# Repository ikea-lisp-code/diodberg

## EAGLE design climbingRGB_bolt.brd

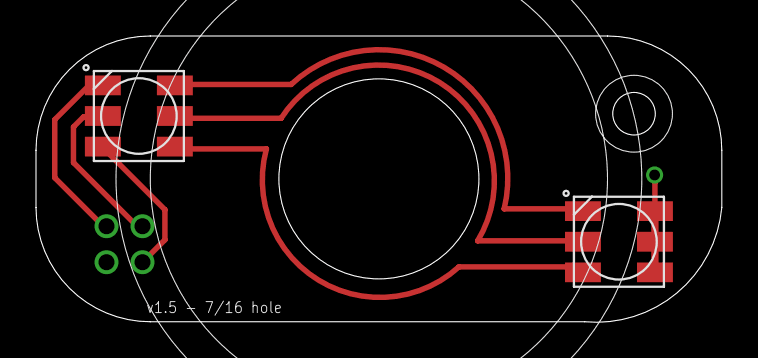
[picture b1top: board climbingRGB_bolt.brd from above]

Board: 2 copper layers, 38.1 x 15.9 mm, 3 parts (1 on the bottom side), 7 nets.

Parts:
LED3, LED4: RGBLED5050
U$1: SWR204-D02; SWR204

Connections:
BLUE: LED4.4, U$1.P$1
GREEN: LED4.6, U$1.P$3
unnamed: LED3.4, LED4.3
unnamed: LED3.6, LED4.1
unnamed: LED3.5, LED4.2
RED: LED4.5, U$1.P$2
VCC: LED3.1, LED3.2, LED3.3, U$1.P$4

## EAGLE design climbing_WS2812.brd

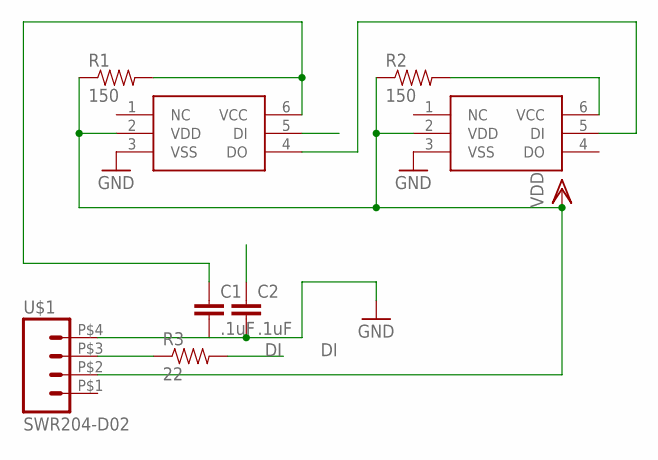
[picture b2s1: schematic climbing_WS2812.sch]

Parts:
C1, C2: .1uF; 0402-CAP
R1, R2: 150; 0402-RES
R3: 22; 0402-RES
U$1: SWR204-D02; SWR204
U$2, U$3: WS2812; RGBLED5050

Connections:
DI: R3.2, U$2.5 (DI)
DODI: U$2.4 (DO), U$3.5 (DI)
GND: C1.2, C2.2, U$1.P$4 (4), U$2.3 (VSS), U$3.3 (VSS)
unnamed: R3.1, U$1.P$3 (3)
VCC: C1.1, R1.2, U$2.6 (VCC)
VCC2: C2.1, R2.2, U$3.6 (VCC)
VDD: R1.1, R2.1, U$1.P$2 (2), U$2.2 (VDD), U$3.2 (VDD)

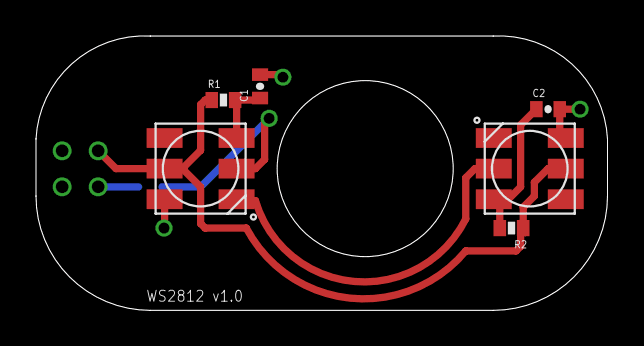
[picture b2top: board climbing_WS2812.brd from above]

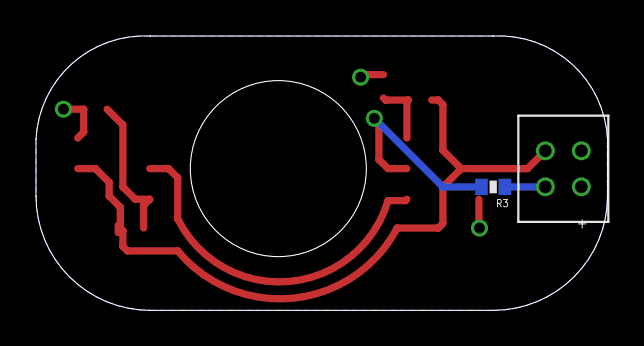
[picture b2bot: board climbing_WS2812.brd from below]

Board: 2 copper layers, 31.8 x 15.2 mm, 8 parts (2 on the bottom side), 7 nets.

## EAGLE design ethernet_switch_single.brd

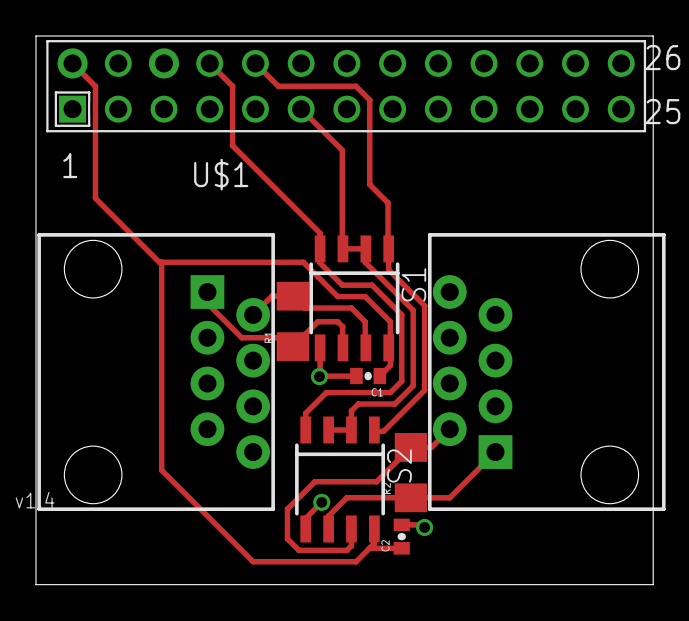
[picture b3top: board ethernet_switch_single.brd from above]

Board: 2 copper layers, 34.3 x 30.5 mm, 9 parts (0 on the bottom side), 9 nets.

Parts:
C1, C2: .1uF; 0402-CAP
E1, E2: RJ45-8PTH; RJ45-8
R1, R2: 100; 1206
S1, S2: 75176B; D_R-PDSO-G8
U$1: RASPBERRY-PI_REV1

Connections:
DATA1+_1: E1.1, R1.1, S1.6
DATA1+_2: E2.1, R2.1, S2.6
DATA1-_1: E1.2, R1.2, S1.7
DATA1-_2: E2.2, R2.2, S2.7
GND: C1.2, C2.2, E1.7, E1.8, E2.7, E2.8, S1.5, S2.5, U$1.6, U$1.9, U$1.14, U$1.20, U$1.25
RE/DE: S1.2, S1.3, S2.2, S2.3, U$1.11
RXI: S1.1, S2.1, U$1.10
TXO: S1.4, S2.4, U$1.8
VCC: C1.1, C2.1, S1.8, S2.8, U$1.2

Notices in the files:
parts and their libraries:
SparkFun-Connectors: Licensing: CC v3.0 Share-Alike You are welcome to use this library for commercial purposes.
